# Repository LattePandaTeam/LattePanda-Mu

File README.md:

# LattePanda Mu Carrier Development Resources

Welcome to the repository of development resources for the LattePanda Mu. With its extensive array of interfaces, you can craft your very own carrier board. While we have provided several reference designs to spark your creativity, a myriad of exciting possibilities awaits your discovery. This repository will be continuously updated to support the development of your personalized carrier board solutions.

## Documentation

- [**LattePanda Mu Compute Module User Guide**](https://docs.lattepanda.com/content/mu_edition/introduction/)

- [**Carrier Board Hardware Design Guide**](https://docs.lattepanda.com/content/mu_edition/design_guide_foreword/)

- [**Carrier Board Compatibility & User Guide**](https://docs.lattepanda.com/content/mu_edition/module_carrier_compatibility/)

- [**LattePanda Website**](https://www.lattepanda.com/)

- [**Join our Discord**](https://discord.gg/RkSvc9g7eU)

## Resource Directory

- **Electricals**: This includes pin descriptions, symbols and footprint libraries, project templates, and example projects.

- **Mechanicals**: This section provides dimensional drawings and 3D models of the LattePanda Mu, its heatsink, and various carrier boards.

- **Software**: BIOS, firmware, drivers, and other related software resources.

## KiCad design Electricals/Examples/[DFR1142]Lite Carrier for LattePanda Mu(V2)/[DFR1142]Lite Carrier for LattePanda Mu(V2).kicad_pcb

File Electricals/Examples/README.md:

# Carrier Board Sample Projects

LattePanda Mu carrier board sample projects for engineers' reference, designed with KiCAD. Please open with KiCAD version 9.0 or higher.

It's recommended to start your design  by referring to the *\[DFR1142\] Lite Carrier for LattePanda Mu(V2)*.

- [Carrier Board Design Guide for LattePanda Mu](https://docs.lattepanda.com/content/mu_edition/design_guide_foreword/)

## Project Files

- **\[DFR1141\] Full EVA Carrier for LattePanda Mu**: The evaluation carrier board that includes nearly all features of the LattePanda Mu, designed to ITX motherboard dimensions, suitable for professional developers.

- **\[DFR1142\] Lite Carrier for LattePanda Mu**: The lite carrier board that includes essential interfaces such as HDMI, USB, PCIe, designed to 3.5-inch embedded motherboard dimensions.

- **\[DFR1142\] Lite Carrier for LattePanda Mu(V2)**: The upgraded version of DFR1142 Lite Carrier. Optimized for evaluation use and small-batch deployment.
  - **Auto Power-On Support:** The system can boots automatically upon receiving power.
  - **New MX1.25-10P Connector:** Designed for compatibility with the DFR1247 LattePanda Smart UPS expansion board.
  - **Side-Mounted Buttons:** Power and Reset buttons have been changed to a side-mounted vertical design to accommodate protective cases better.
  - **External Control Headers:** Added pin headers for external power control and status indication.
  - **Sleep Indicator:** Added a dedicated LED for sleep mode status.
  - **BIOS Flash Chip Footprint:** Added a footprint for a carrier board BIOS flash chip (not soldered by default) for advanced customization.

- **\[DFR1144\] GPU Carrier for LattePanda Mu**: The GPU carrier board features six video output ports, supports Type A/B MXM standard graphics cards, and adopts the 3.5-inch embedded motherboard form factor. It is suitable for local AI inference or multi-screen display matrix applications.

- **\[DFR1293\] Mini Carrier for LattePanda Mu \\ Mu Ultra**: a compact, highly expandable carrier board compatible with the LattePanda Mu and LattePanda Mu Ultra compute module. It integrates commonly used ports such as two full-featured Type-C, 2.5G Ethernet, USB 3.2 Gen2, OCuLink, M.2 M Key, M.2 E Key, HDMI, and GPIO. 

## Compatibility List

Compatibility varies between different compute modules and different carrier boards. Please visit the [**Carrier Board Docs**](https://docs.lattepanda.com/content/mu_edition/module_carrier_compatibility/) for the compatibility list.

## Mechanical Files

For the 2D drawings and 3D models of the carrier boards, please see [Mechanicals/Carrier-Boards](../../Mechanicals/Carrier-Boards).

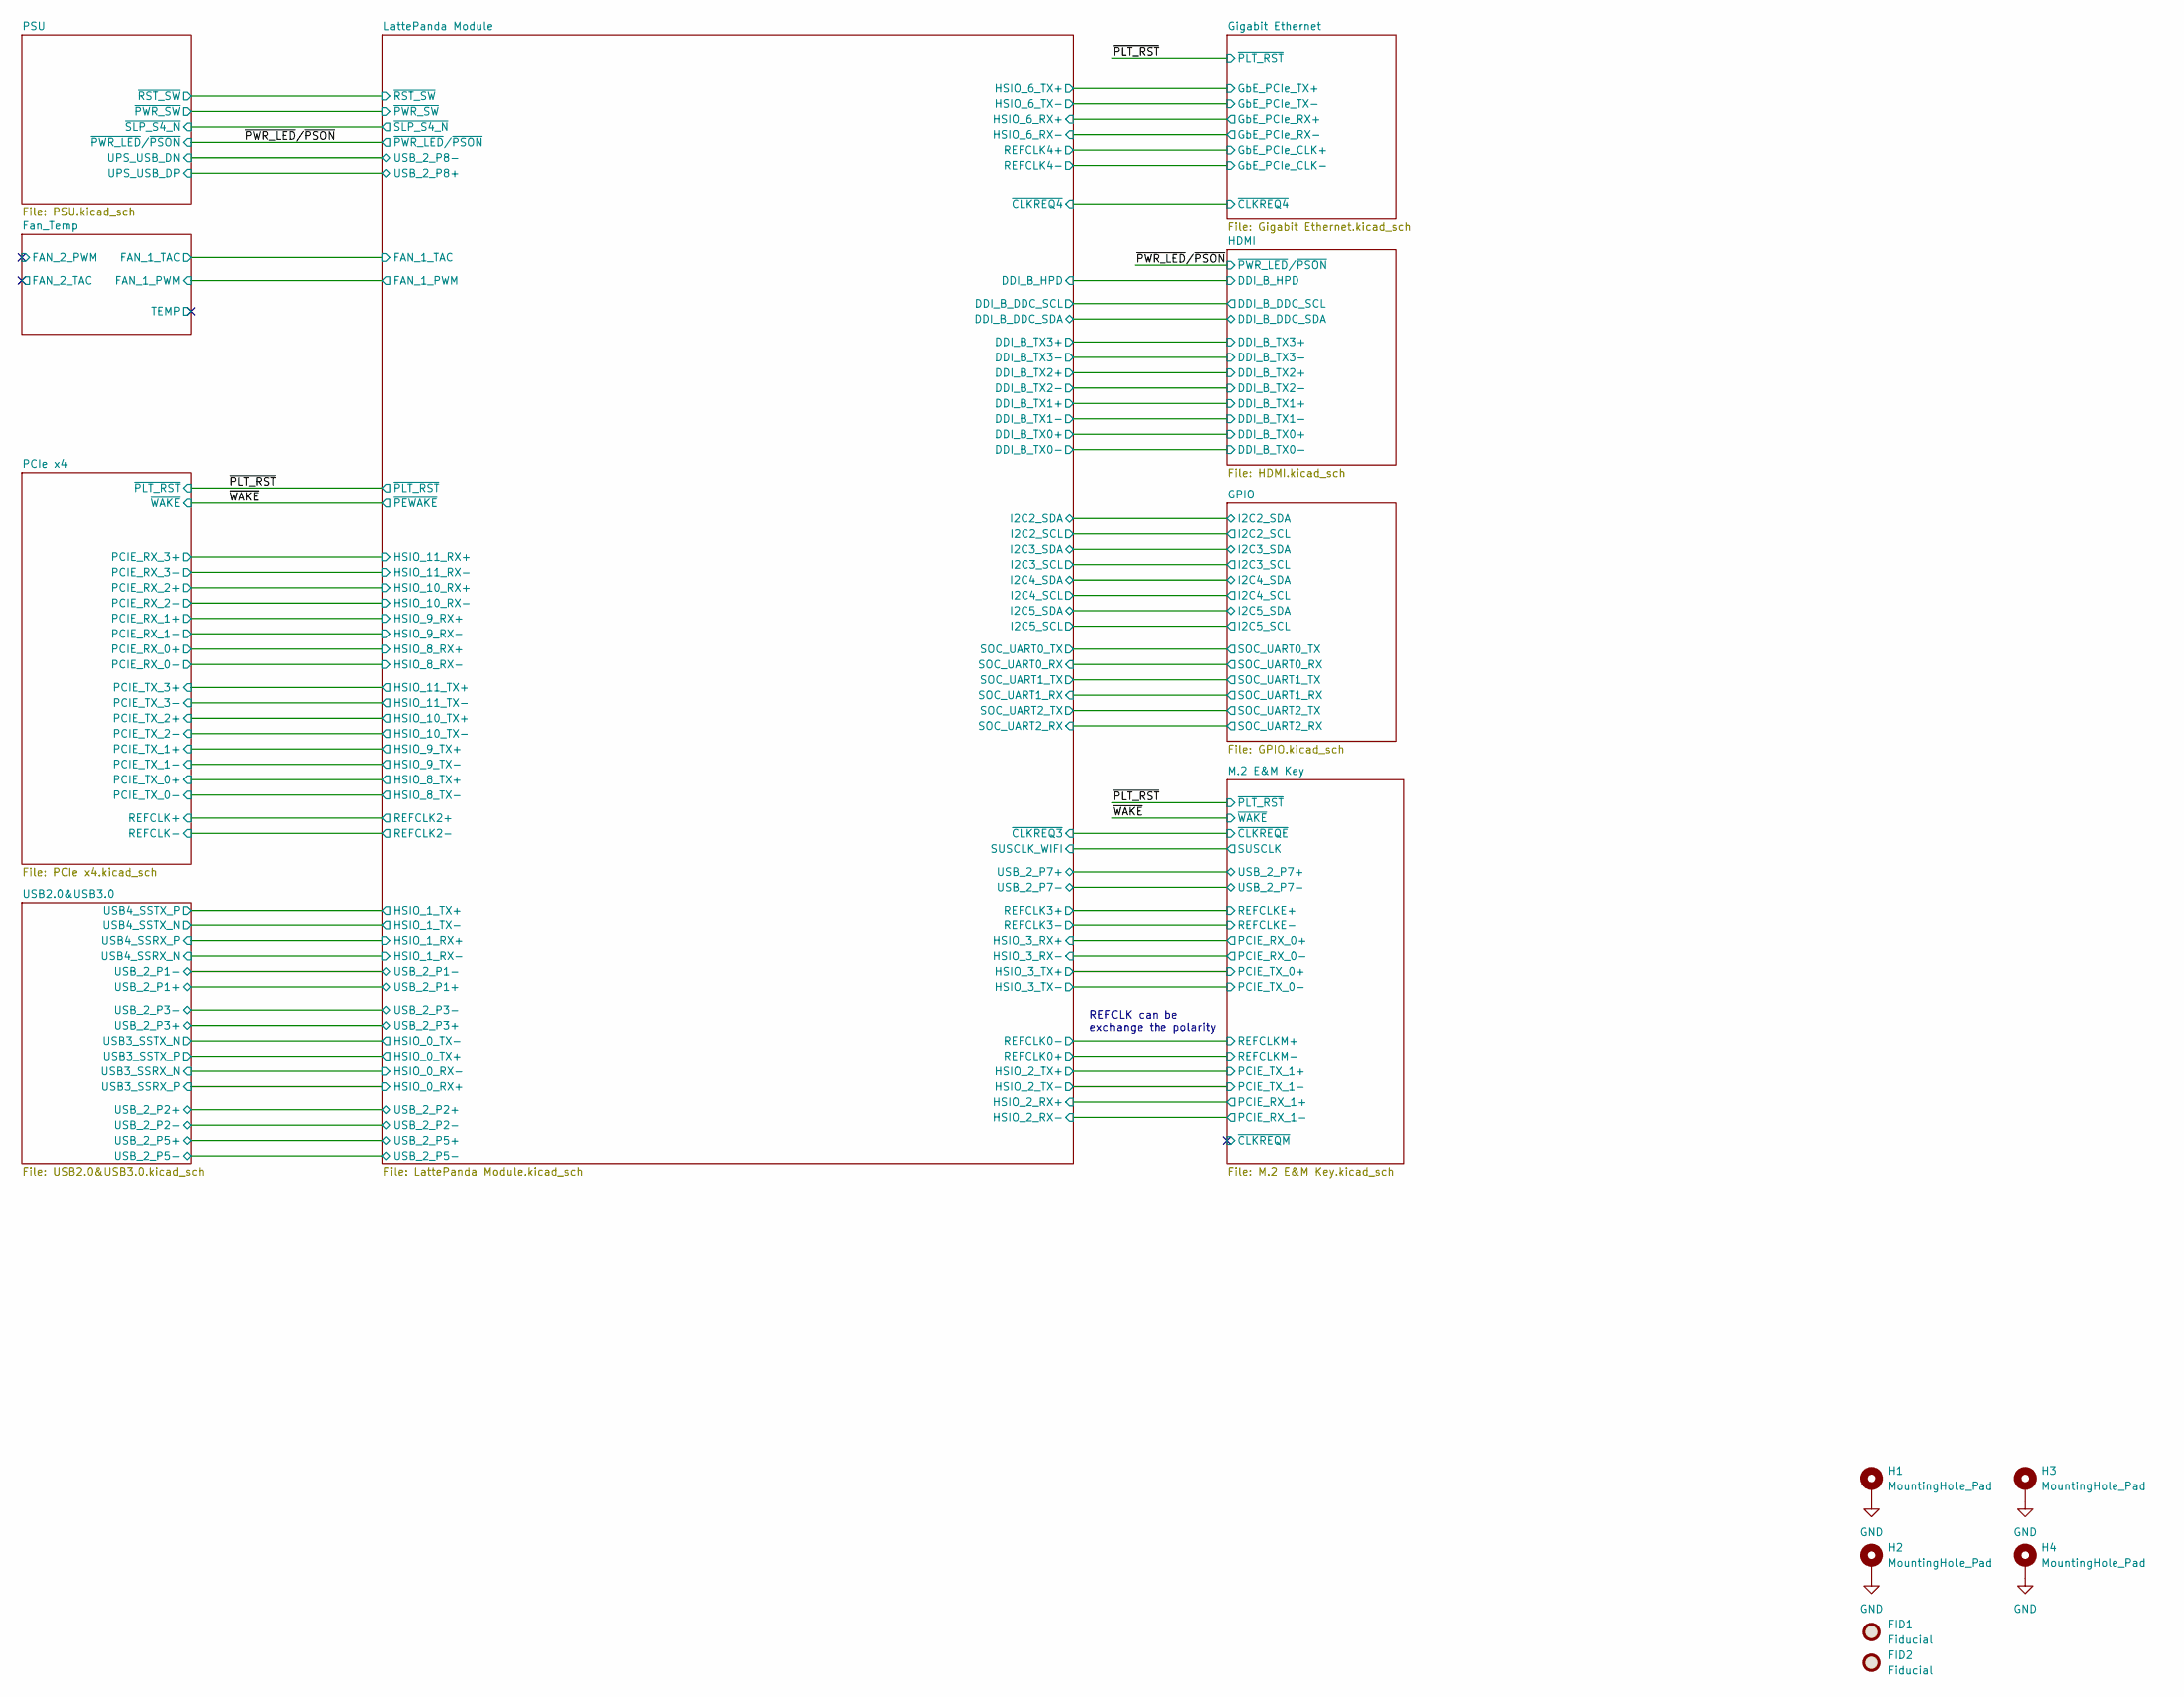
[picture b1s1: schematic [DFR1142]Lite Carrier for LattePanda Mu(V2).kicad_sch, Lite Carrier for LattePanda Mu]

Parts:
FID1, FID2: Fiducial; Fiducial_1mm_Mask2mm
H1, H2, H3, H4: MountingHole_Pad; MountingHole_3.2mm_M3_Pad_Via

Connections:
GND: H1.1, H2.1, H3.1, H4.1; also elsewhere on the board

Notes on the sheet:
REFCLK can be exchange the polarity

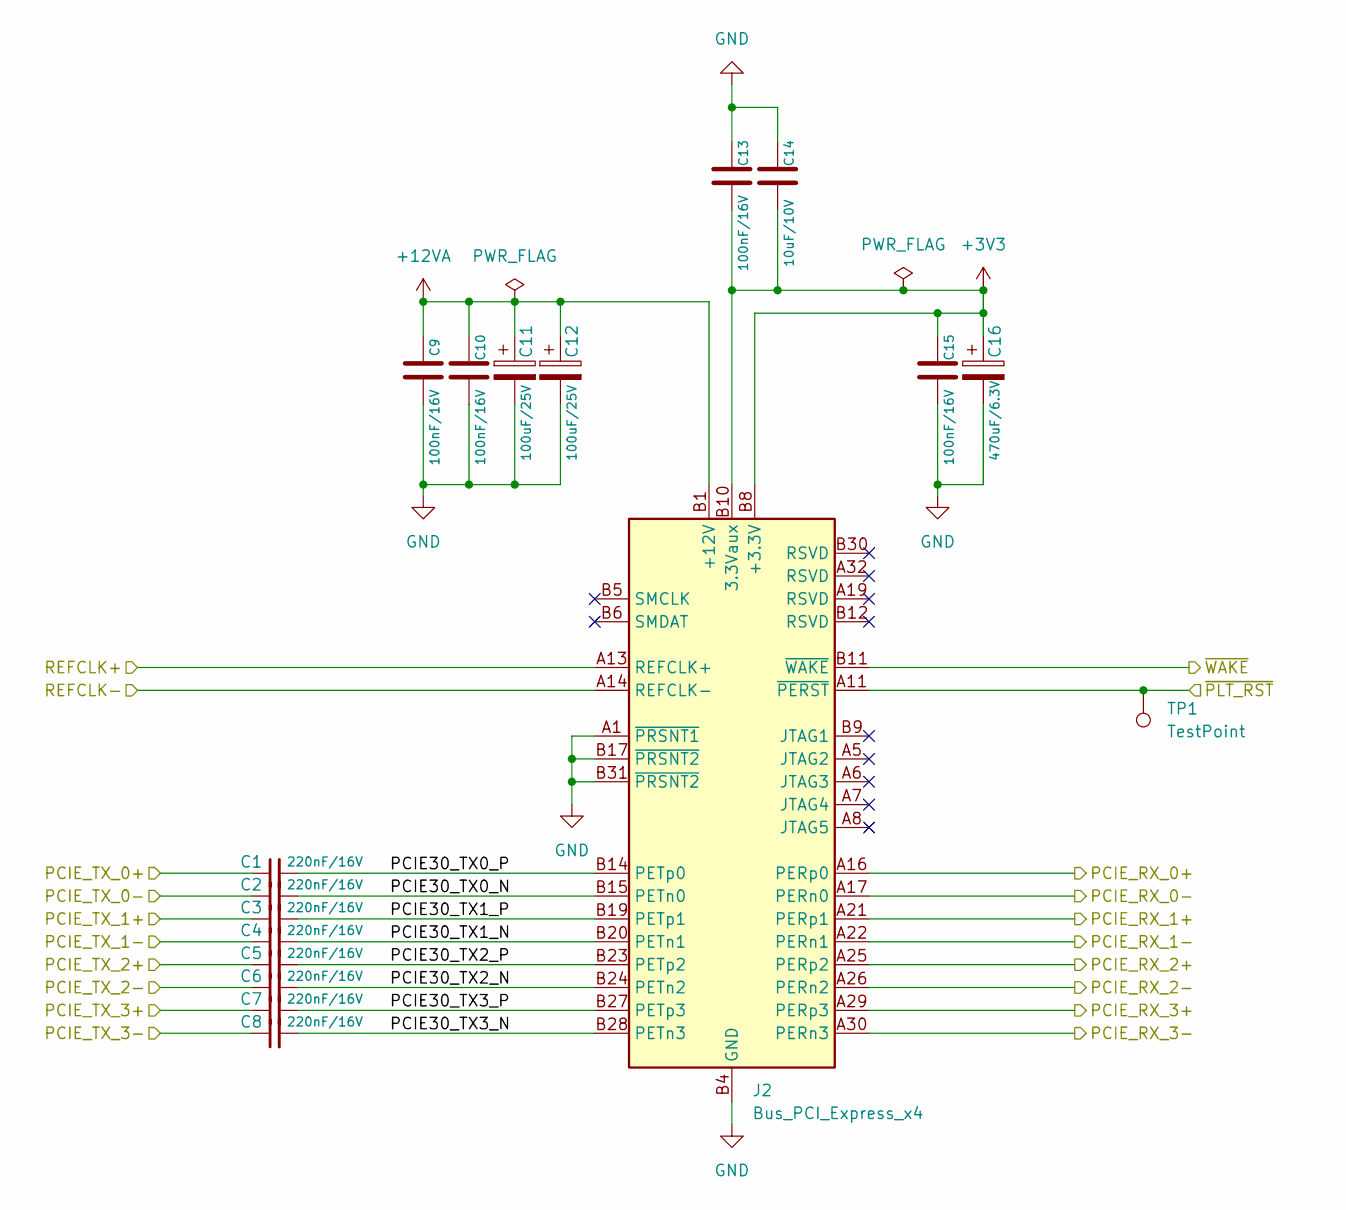
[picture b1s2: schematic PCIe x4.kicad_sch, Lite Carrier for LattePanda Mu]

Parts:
C1, C2, C3, C4, C5, C6, C7, C8: 220nF/16V; C_0402_1005Metric
C9, C10, C13, C15: 100nF/16V; C_0402_1005Metric
C11, C12: 100uF/25V; CP_Elec_6.3x7.7
C14: 10uF/10V; C_0402_1005Metric
C16: 470uF/6.3V; CP_Elec_6.3x7.7
J2: Bus_PCI_Express_x4; PCIe_x4_Gen3Slot_Connectors
TP1: TestPoint; TestPoint_Pad_D1.5mm

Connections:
+3V3: C13.2, C14.2, C15.1, C16.1, J2.A9 (+3.3V), J2.A10 (+3.3V), J2.B8 (+3.3V), J2.B10 (3.3Vaux); also elsewhere on the board
+12VA: C9.1, C10.1, C11.1, C12.1, J2.A2 (+12V), J2.A3 (+12V), J2.B1 (+12V), J2.B2 (+12V), J2.B3 (+12V); also elsewhere on the board
/LattePanda Module/HSIO_8_RX+: J2.A16 (PERp0); also elsewhere on the board
/LattePanda Module/HSIO_8_RX-: J2.A17 (PERn0); also elsewhere on the board
/LattePanda Module/HSIO_8_TX+: C1.1; also elsewhere on the board
/LattePanda Module/HSIO_8_TX-: C2.1; also elsewhere on the board
/LattePanda Module/HSIO_9_RX+: J2.A21 (PERp1); also elsewhere on the board
/LattePanda Module/HSIO_9_RX-: J2.A22 (PERn1); also elsewhere on the board
/LattePanda Module/HSIO_9_TX+: C3.1; also elsewhere on the board
/LattePanda Module/HSIO_9_TX-: C4.1; also elsewhere on the board
/LattePanda Module/HSIO_10_RX+: J2.A25 (PERp2); also elsewhere on the board
/LattePanda Module/HSIO_10_RX-: J2.A26 (PERn2); also elsewhere on the board
/LattePanda Module/HSIO_10_TX+: C5.1; also elsewhere on the board
/LattePanda Module/HSIO_10_TX-: C6.1; also elsewhere on the board
/LattePanda Module/HSIO_11_RX+: J2.A29 (PERp3); also elsewhere on the board
/LattePanda Module/HSIO_11_RX-: J2.A30 (PERn3); also elsewhere on the board
/LattePanda Module/HSIO_11_TX+: C7.1; also elsewhere on the board
/LattePanda Module/HSIO_11_TX-: C8.1; also elsewhere on the board
/LattePanda Module/REFCLK2+: J2.A13 (REFCLK+); also elsewhere on the board
/LattePanda Module/REFCLK2-: J2.A14 (REFCLK-); also elsewhere on the board
/PCIe x4/PCIE30_TX0_N: C2.2, J2.B15 (PETn0)
/PCIe x4/PCIE30_TX0_P: C1.2, J2.B14 (PETp0)
/PCIe x4/PCIE30_TX1_N: C4.2, J2.B20 (PETn1)
/PCIe x4/PCIE30_TX1_P: C3.2, J2.B19 (PETp1)
/PCIe x4/PCIE30_TX2_N: C6.2, J2.B24 (PETn2)
/PCIe x4/PCIE30_TX2_P: C5.2, J2.B23 (PETp2)
/PCIe x4/PCIE30_TX3_N: C8.2, J2.B28 (PETn3)
/PCIe x4/PCIE30_TX3_P: C7.2, J2.B27 (PETp3)
/~PLT_RST: J2.A11 (~PERST), TP1.1; also elsewhere on the board
/~WAKE: J2.B11 (~WAKE); also elsewhere on the board
GND: C9.2, C10.2, C11.2, C12.2, C13.1, C14.1, C15.2, C16.2, J2.A1 (~PRSNT1), J2.A4 (GND), J2.A12 (GND), J2.A15 (GND), J2.A18 (GND), J2.A20 (GND), J2.A23 (GND), J2.A24 (GND), J2.A27 (GND), J2.A28 (GND), J2.A31 (GND), J2.B4 (GND), J2.B7 (GND), J2.B13 (GND), J2.B16 (GND), J2.B17 (~PRSNT2), J2.B18 (GND), J2.B21 (GND), J2.B22 (GND), J2.B25 (GND), J2.B26 (GND), J2.B29 (GND), J2.B31 (~PRSNT2), J2.B32 (GND); also elsewhere on the board

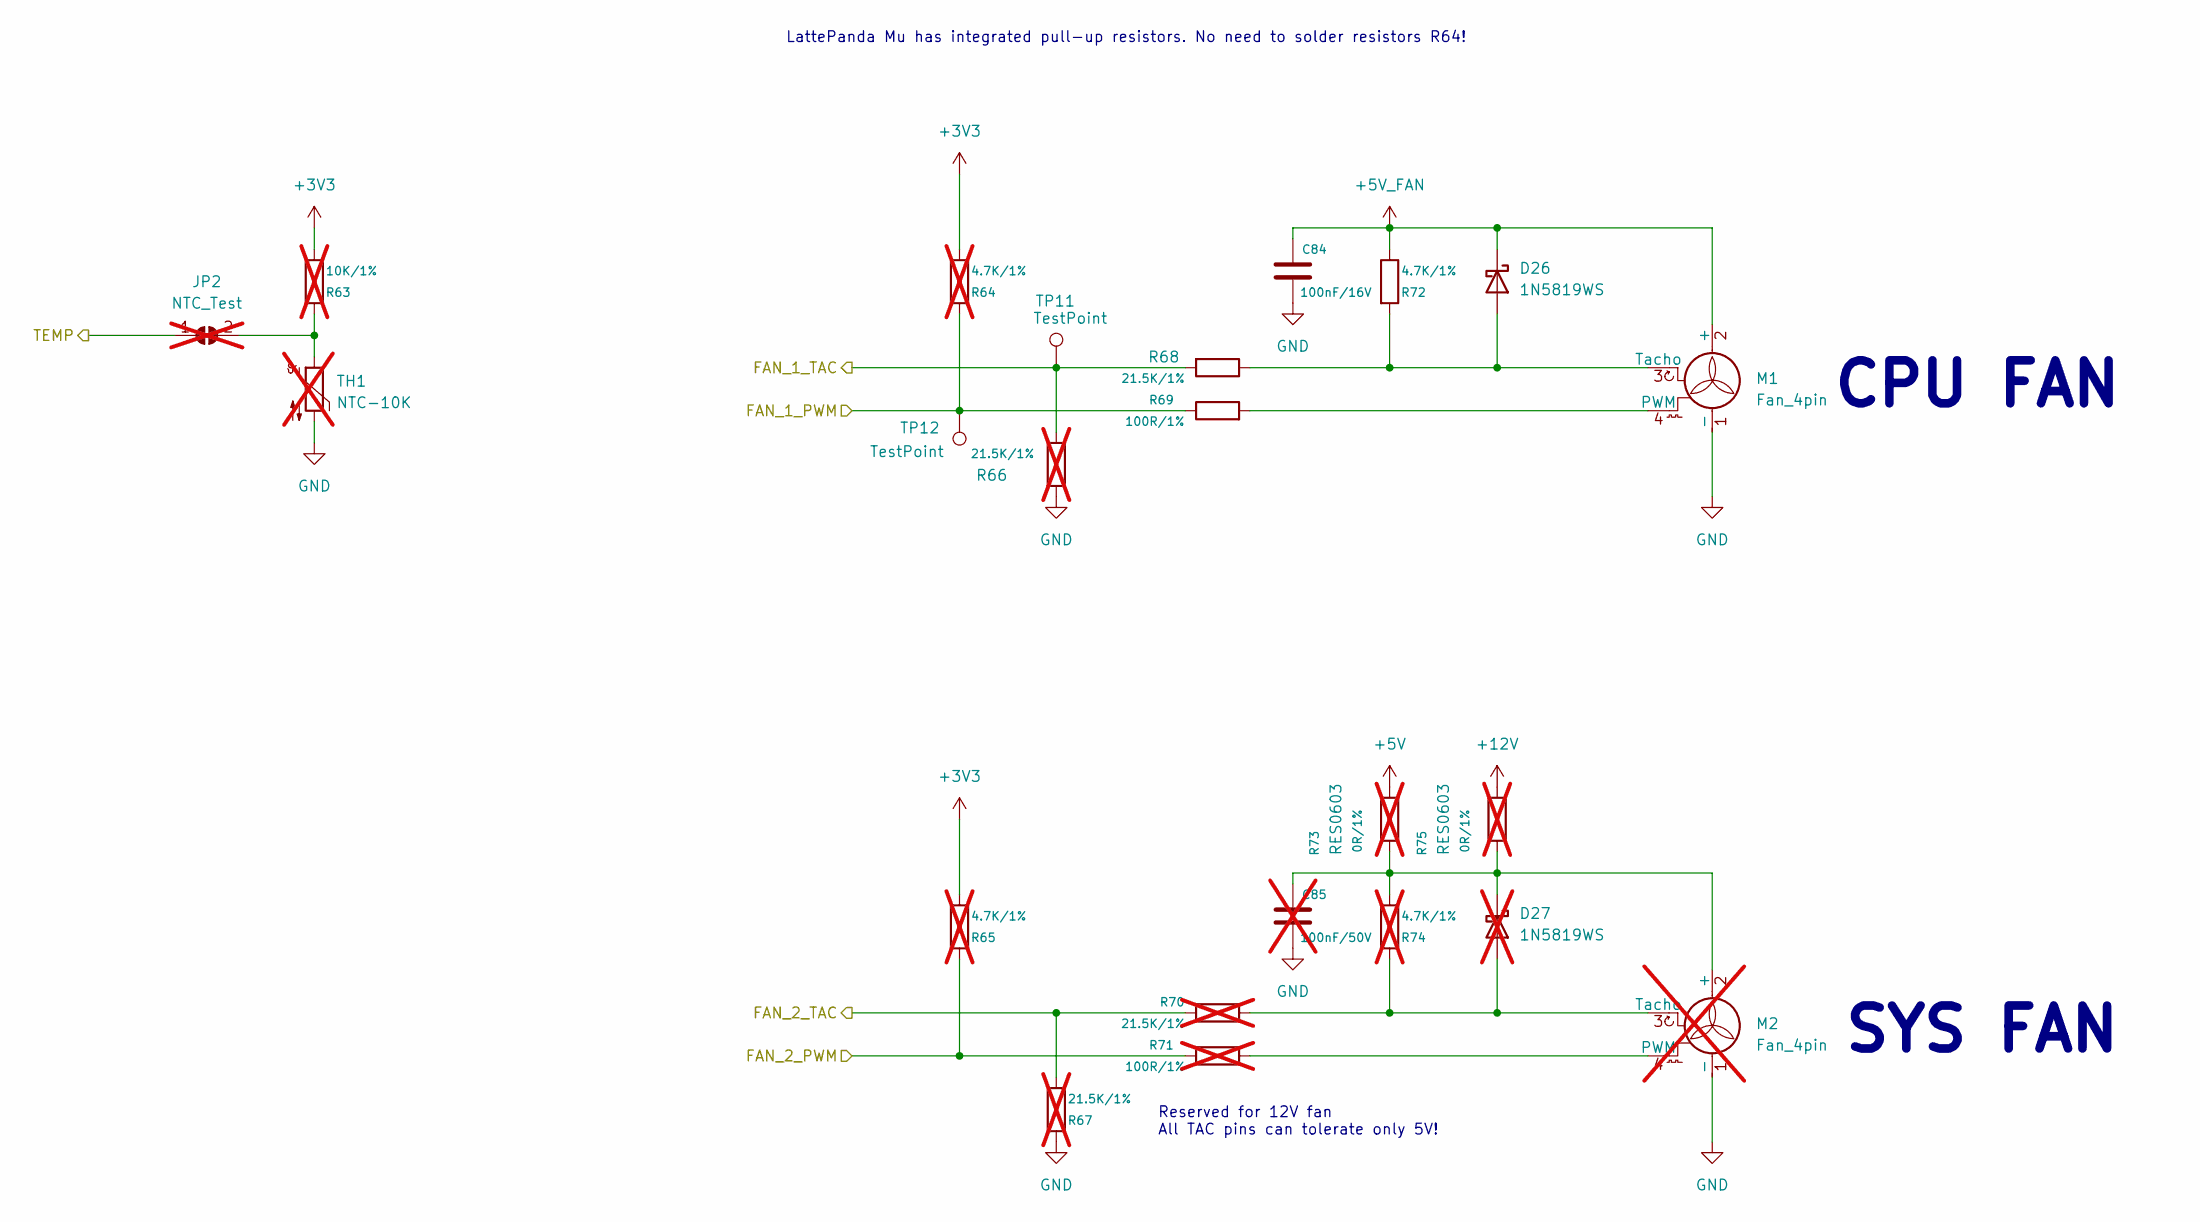
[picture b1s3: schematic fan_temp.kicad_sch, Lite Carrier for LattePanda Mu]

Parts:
C84: 100nF/16V; C_0402_1005Metric
C85: 100nF/50V; C_0402_1005Metric; not fitted
D26: 1N5819WS; D_SOD-323
D27: 1N5819WS; D_SOD-323; not fitted
JP2: NTC_Test; SolderJumper-2_P1.3mm_Open_RoundedPad1.0x1.5mm; not fitted
M1: Fan_4pin; JST_PH_B4B-PH-K_1x04_P2.00mm_Vertical
M2: Fan_4pin; JST_PH_B4B-PH-K_1x04_P2.00mm_Vertical; not fitted
R63: 10K/1%; R_0402_1005Metric; not fitted
R64, R65, R74: 4.7K/1%; R_0402_1005Metric; not fitted
R66, R67, R70: 21.5K/1%; R_0402_1005Metric; not fitted
R68: 21.5K/1%; R_0402
R69: 100R/1%; R_0402
R71: 100R/1%; R_0402_1005Metric; not fitted
R72: 4.7K/1%; R_0402
R73, R75: 0R/1%; RES0603; not fitted
TH1: NTC-10K; R_0603_1608Metric; not fitted
TP11, TP12: TestPoint; TestPoint_Pad_D1.5mm

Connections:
+3V3: R63.1, R64.1, R65.1; also elsewhere on the board
+5V_FAN: C84.1, D26.1 (K), M1.2 (+), R72.1; also elsewhere on the board
/Fan_Temp/FAN_1_PWM: R64.2, R69.1, TP12.1; also elsewhere on the board
/Fan_Temp/FAN_1_TAC: R66.1, R68.2, TP11.1; also elsewhere on the board
GND: C84.2, C85.2, M1.1 (-), M2.1 (-), R66.2, R67.2, TH1.2; also elsewhere on the board
unnamed: C85.1, D27.1 (K), M2.2 (+), R73.1, R74.1, R75.1
unnamed: D26.2 (A), M1.3 (Tacho), R68.1, R72.2
unnamed: D27.2 (A), M2.3 (Tacho), R70.2, R74.2
unnamed: JP2.2 (B), R63.2, TH1.1
unnamed: M1.4 (PWM), R69.2
unnamed: M2.4 (PWM), R71.2
unnamed: R65.2, R71.1
unnamed: R67.1, R70.1

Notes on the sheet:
CPU FAN
Reserved for 12V fan All TAC pins can tolerate only 5V!
SYS FAN
LattePanda Mu has integrated pull-up resistors. No need to solder resistors R64!
